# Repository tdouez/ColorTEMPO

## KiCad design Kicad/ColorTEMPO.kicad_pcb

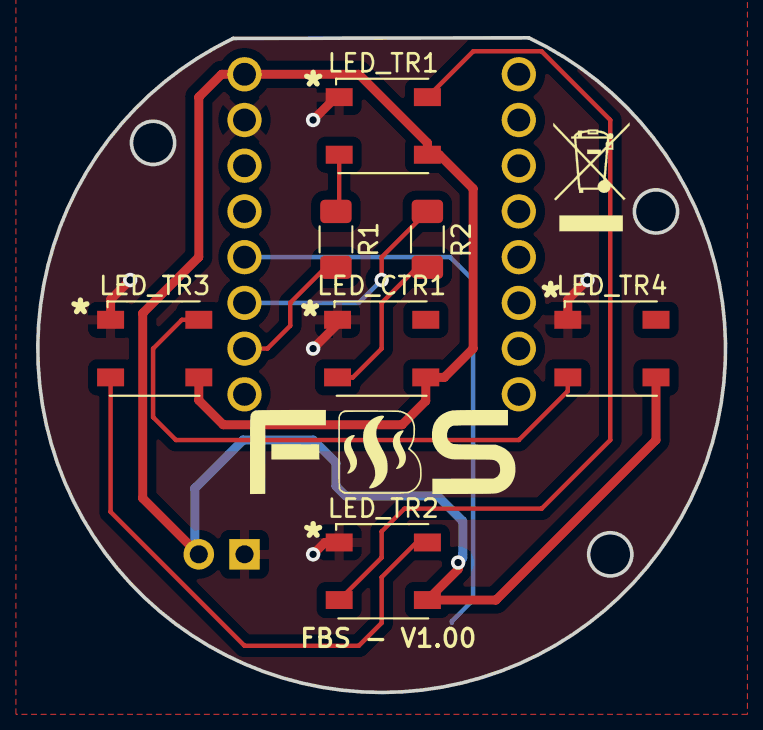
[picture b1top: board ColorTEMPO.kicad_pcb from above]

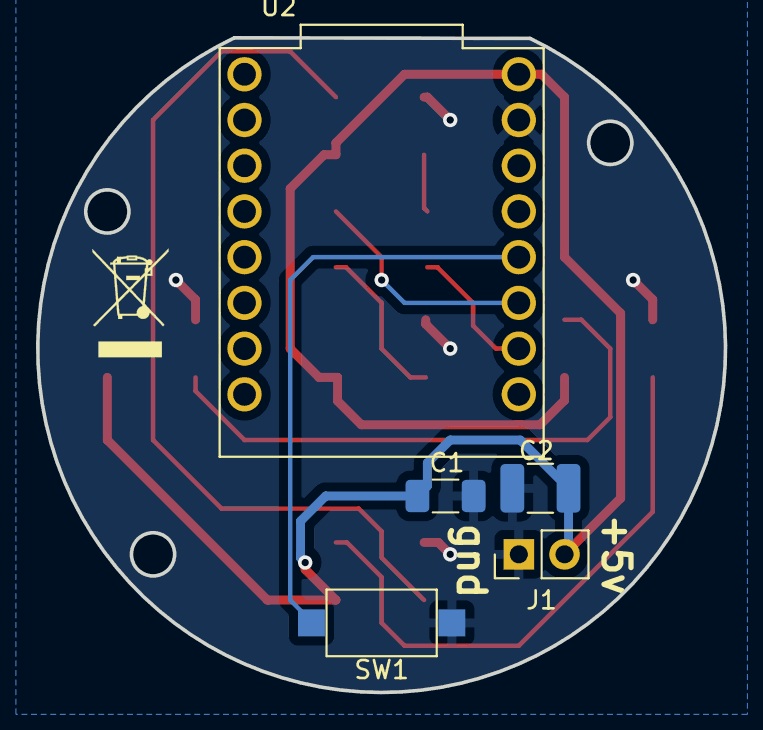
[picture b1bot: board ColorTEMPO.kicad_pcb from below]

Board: 2 copper layers, 38.2 x 36.4 mm, 12 parts (5 on the bottom side), 10 nets.

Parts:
C1: 100nF; C_1206_3216Metric_Pad1.33x1.80mm_HandSolder
C2: 22uF; C_1210_3225Metric_Pad1.33x2.70mm_HandSolder
J1: Conn_01x02; PinHeader_1x02_P2.54mm_Vertical
LED_CTR1: Inolux_IN-PI554FCH; LED_Inolux_IN-PI554FCH_PLCC4_5.0x5.0mm_P3.2mm
LED_TR1, LED_TR2, LED_TR3, LED_TR4: Inolux_IN-PI554FCH; LED_Inolux_IN-PI554FCH_PLCC4_5.0x5.0mm_P3.2mm
R1, R2: 470; R_1206_3216Metric_Pad1.30x1.75mm_HandSolder
SW1: SW_Push; SW_SPST_CK_RS282G05A3
U2: ESP32-C3_SUPERMINI; MODULE_ESP32-C3_SUPERMINI

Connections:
+5V: C1.1, C2.1, J1.2, LED_CTR1.3 (VDD), LED_TR1.3 (VDD), LED_TR2.3 (VDD), LED_TR3.3 (VDD), LED_TR4.3 (VDD), U2.5V
GND: C1.2, C2.2, J1.1, LED_CTR1.1 (VSS), LED_TR1.1 (VSS), LED_TR2.1 (VSS), LED_TR3.1 (VSS), LED_TR4.1 (VSS), SW1.1, U2.G (GND)
LED_CENTRE: LED_CTR1.2 (DIN), R2.1
LED_TOUR: LED_TR1.2 (DIN), R1.1
unnamed: LED_TR1.4 (DO), LED_TR2.2 (DIN)
unnamed: LED_TR2.4 (DO), LED_TR3.2 (DIN)
unnamed: LED_TR3.4 (DO), LED_TR4.2 (DIN)
unnamed: R1.2, U2.1 (GPIO1)
unnamed: R2.2, U2.2 (GPIO2)
unnamed: SW1.2, U2.3 (GPIO3)

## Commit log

2024-03-04 V1.0
    V1.0
2024-03-07 V1.0.0
2024-09-05 v1.1.0
    Changement de serveur pour la récupération de la couleur TEMPO
2024-12-05 V1.1.1
    Ajout test reset au démarrage du module
